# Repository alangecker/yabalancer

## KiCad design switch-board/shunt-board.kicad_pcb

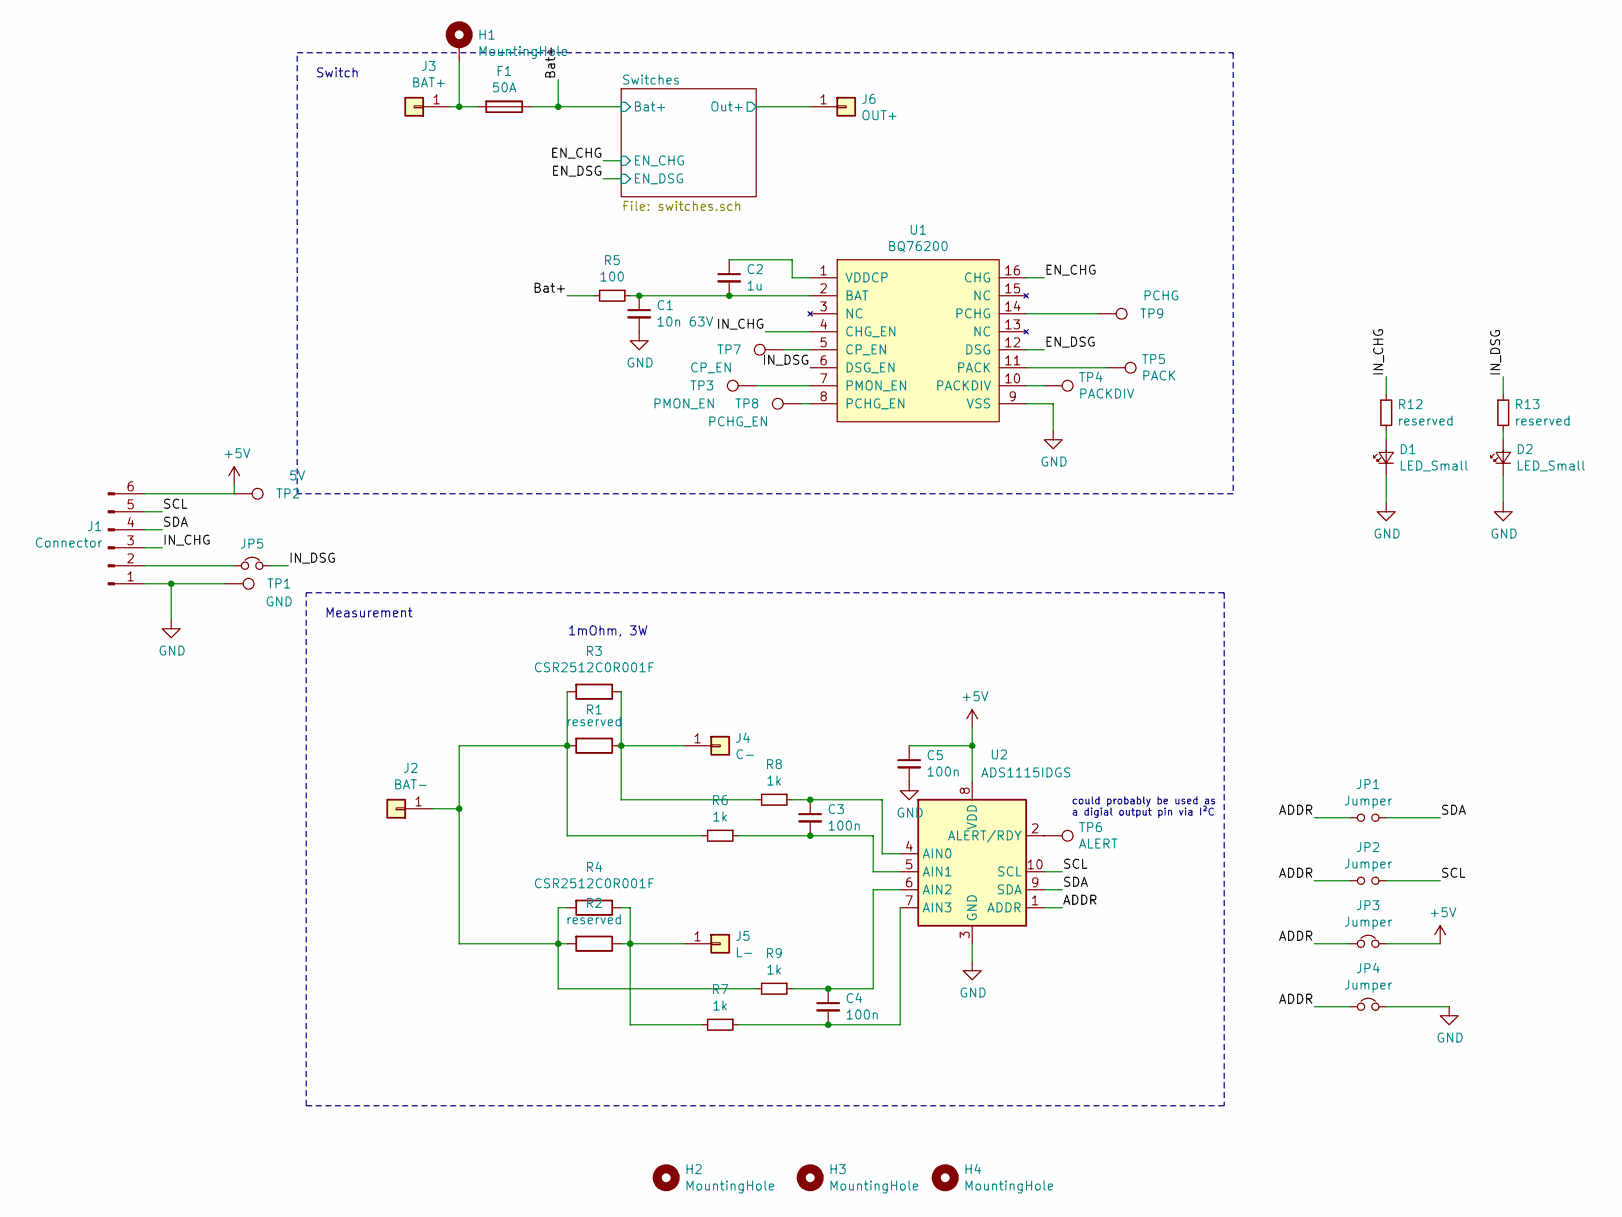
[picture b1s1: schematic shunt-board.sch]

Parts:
C1: 10n 63V; C_0805_2012Metric_Pad1.15x1.40mm_HandSolder
C2: 1u; C_0805_2012Metric_Pad1.15x1.40mm_HandSolder
C3, C4, C5: 100n; C_0805_2012Metric_Pad1.15x1.40mm_HandSolder
D1, D2: LED_Small; LED_1206_3216Metric_Pad1.42x1.75mm_HandSolder
F1: 50A; midiFuseHolder
H1, H2, H3, H4: MountingHole; MountingHole_4mm_Pad_Via
J1: Connector; JST_XH_B6B-XH-A_1x06_P2.50mm_Vertical
J2: BAT-; M5_screw_terminal
J3: BAT+; M5_screw_terminal
J4: C-; M5_screw_terminal
J5: L-; M5_screw_terminal
J6: OUT+; M5_screw_terminal
JP1, JP2: Jumper; SolderJumper-2_P1.3mm_Open_RoundedPad1.0x1.5mm
JP3, JP4: Jumper; SolderJumper-2_P1.3mm_Bridged_RoundedPad1.0x1.5mm
JP5: Jumper_NC_Small; SolderJumper-2_P1.3mm_Bridged2Bar_RoundedPad1.0x1.5mm
R1, R2: reserved; R_2512_6332Metric_Pad1.52x3.35mm_HandSolder
R3, R4: CSR2512C0R001F; R_2512_6332Metric_Pad1.52x3.35mm_HandSolder
R5: 100; R_0805_2012Metric
R6, R7, R8, R9: 1k; R_0805_2012Metric
R12, R13: reserved; R_0805_2012Metric_Pad1.15x1.40mm_HandSolder
TP1: GND; TestPoint_Pad_1.0x1.0mm
TP2: 5V; TestPoint_Pad_1.0x1.0mm
TP3: PMON_EN; TestPoint_Pad_1.0x1.0mm
TP4: PACKDIV; TestPoint_Pad_1.0x1.0mm
TP5: PACK; TestPoint_Pad_1.0x1.0mm
TP6: ALERT; TestPoint_Pad_1.0x1.0mm
TP7: CP_EN; TestPoint_Pad_1.0x1.0mm
TP8: PCHG_EN; TestPoint_Pad_1.0x1.0mm
TP9: PCHG; TestPoint_Pad_1.0x1.0mm
U1: BQ76200; TSSOP-16_4.4x5mm_P0.65mm
U2: ADS1115IDGS; TSSOP-10_3x3mm_P0.5mm

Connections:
+5V: C5.1, J1.6, JP3.2, TP2.1, U2.8 (VDD)
/ADDR: JP1.1, JP2.1, JP3.1, JP4.1, U2.1 (ADDR)
/Bat+: F1.1, R5.2; also elsewhere on the board
/EN_CHG: U1.16 (CHG); also elsewhere on the board
/EN_DSG: U1.12 (DSG); also elsewhere on the board
/IN_CHG: J1.3, R12.1, U1.4 (CHG_EN)
/IN_DSG: JP5.2, R13.1, U1.6 (DSG_EN)
/SCL: J1.5, JP2.2, U2.10 (SCL)
/SDA: J1.4, JP1.2, U2.9 (SDA)
/Switches/Out+: J6.1; also elsewhere on the board
GND: C1.2, C5.2, D1.1 (K), D2.1 (K), J1.1, JP4.2, TP1.1, U1.9 (VSS), U2.3 (GND)
unnamed: C1.1, C2.2, R5.1, U1.2 (BAT)
unnamed: C2.1, U1.1 (VDDCP)
unnamed: C3.1, R8.1, U2.4 (AIN0)
unnamed: C3.2, R6.1, U2.5 (AIN1)
unnamed: C4.1, R9.1, U2.6 (AIN2)
unnamed: C4.2, R7.1, U2.7 (AIN3)
unnamed: D1.2 (A), R12.2
unnamed: D2.2 (A), R13.2
unnamed: F1.2, H1.1, J3.1
unnamed: J1.2, JP5.1
unnamed: J2.1, R1.2, R2.2, R3.2, R4.2, R6.2, R9.2
unnamed: J4.1, R1.1, R3.1, R8.2
unnamed: J5.1, R2.1, R4.1, R7.2
unnamed: TP3.1, U1.7 (PMON_EN)
unnamed: TP4.1, U1.10 (PACKDIV)
unnamed: TP5.1, U1.11 (PACK)
unnamed: TP6.1, U2.2 (ALERT/RDY)
unnamed: TP7.1, U1.5 (CP_EN)
unnamed: TP8.1, U1.8 (PCHG_EN)
unnamed: TP9.1, U1.14 (PCHG)

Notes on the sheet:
Measurement
Switch
1mOhm, 3W
could probably be used as a digial output pin via I²C

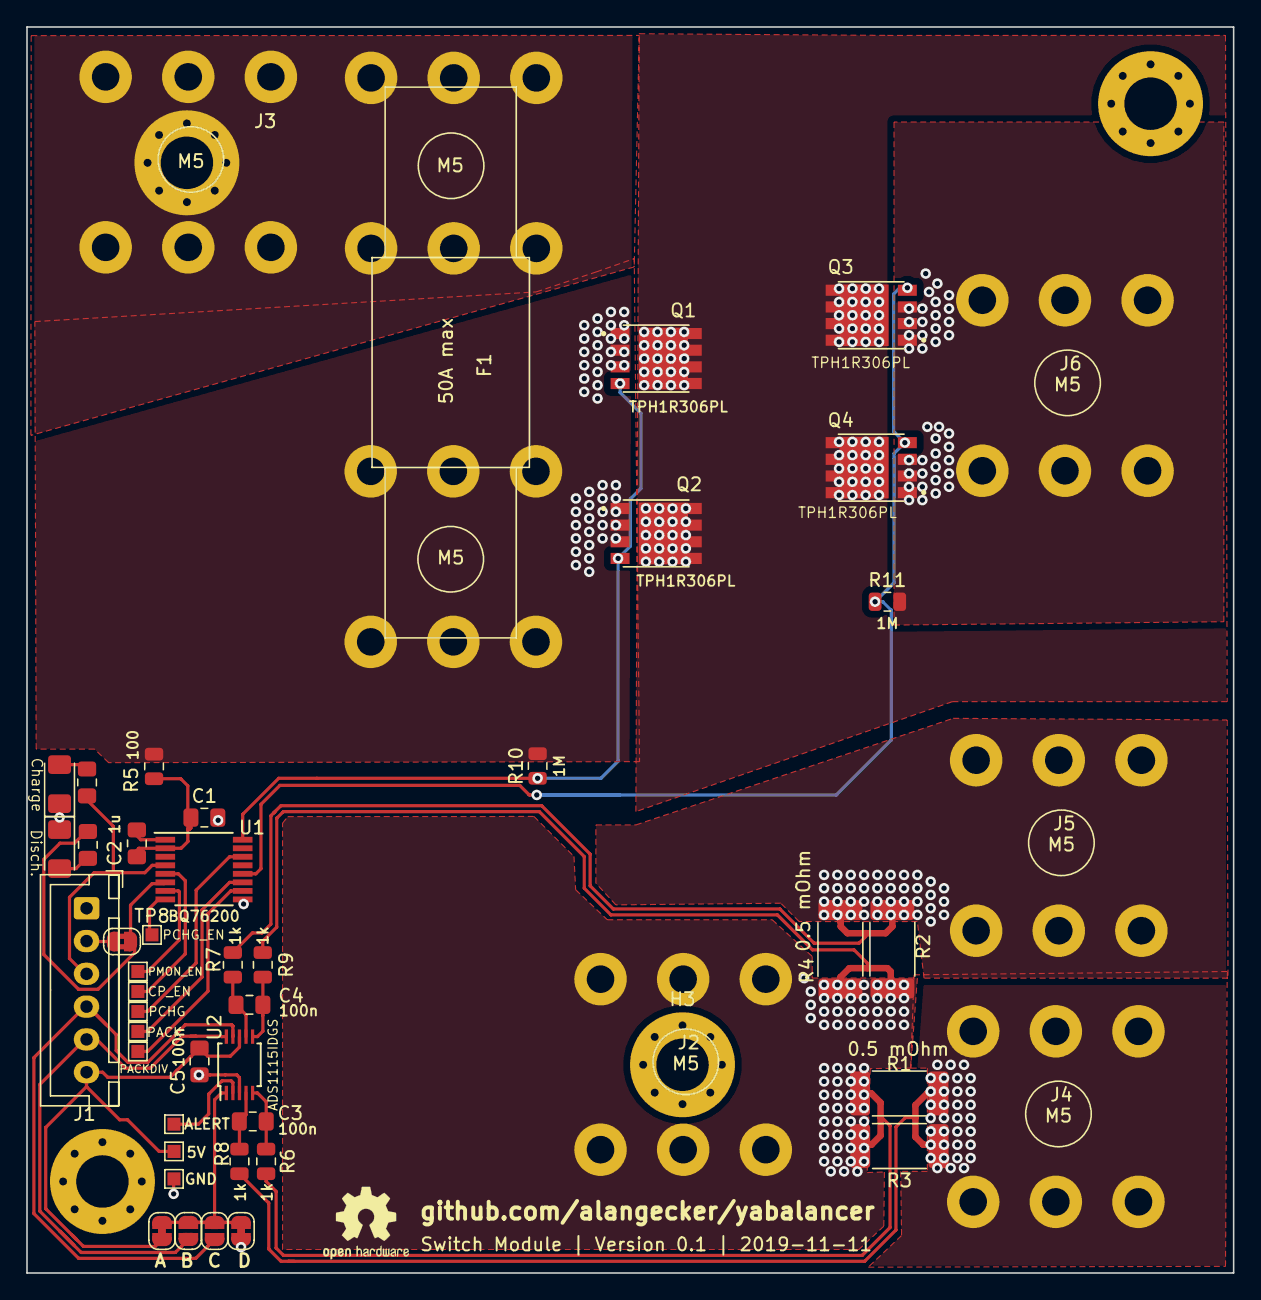
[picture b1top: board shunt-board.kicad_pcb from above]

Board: 2 copper layers, 92.0 x 95.0 mm, 51 parts (0 on the bottom side), 32 nets.

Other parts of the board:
Q1, Q2, Q3, Q4: TPH1R306PL; TRANS_TPHR8504PL,L1Q
R10, R11: 1M; R_0805_2012Metric

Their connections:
/Bat+: Q1.1, Q1.2, Q1.3, Q2.1, Q2.2, Q2.3, R10.2; also elsewhere on the board
/EN_CHG: Q1.4, Q2.4, R10.1; also elsewhere on the board
/EN_DSG: Q3.4, Q4.4, R11.1; also elsewhere on the board
/Switches/Out+: Q3.1, Q3.2, Q3.3, Q4.1, Q4.2, Q4.3, R11.2; also elsewhere on the board
unnamed: Q1.5, Q1.6, Q1.7, Q1.8, Q1.9, Q2.5, Q2.6, Q2.7, Q2.8, Q2.9, Q3.5, Q3.6, Q3.7, Q3.8, Q3.9, Q4.5, Q4.6, Q4.7, Q4.8, Q4.9

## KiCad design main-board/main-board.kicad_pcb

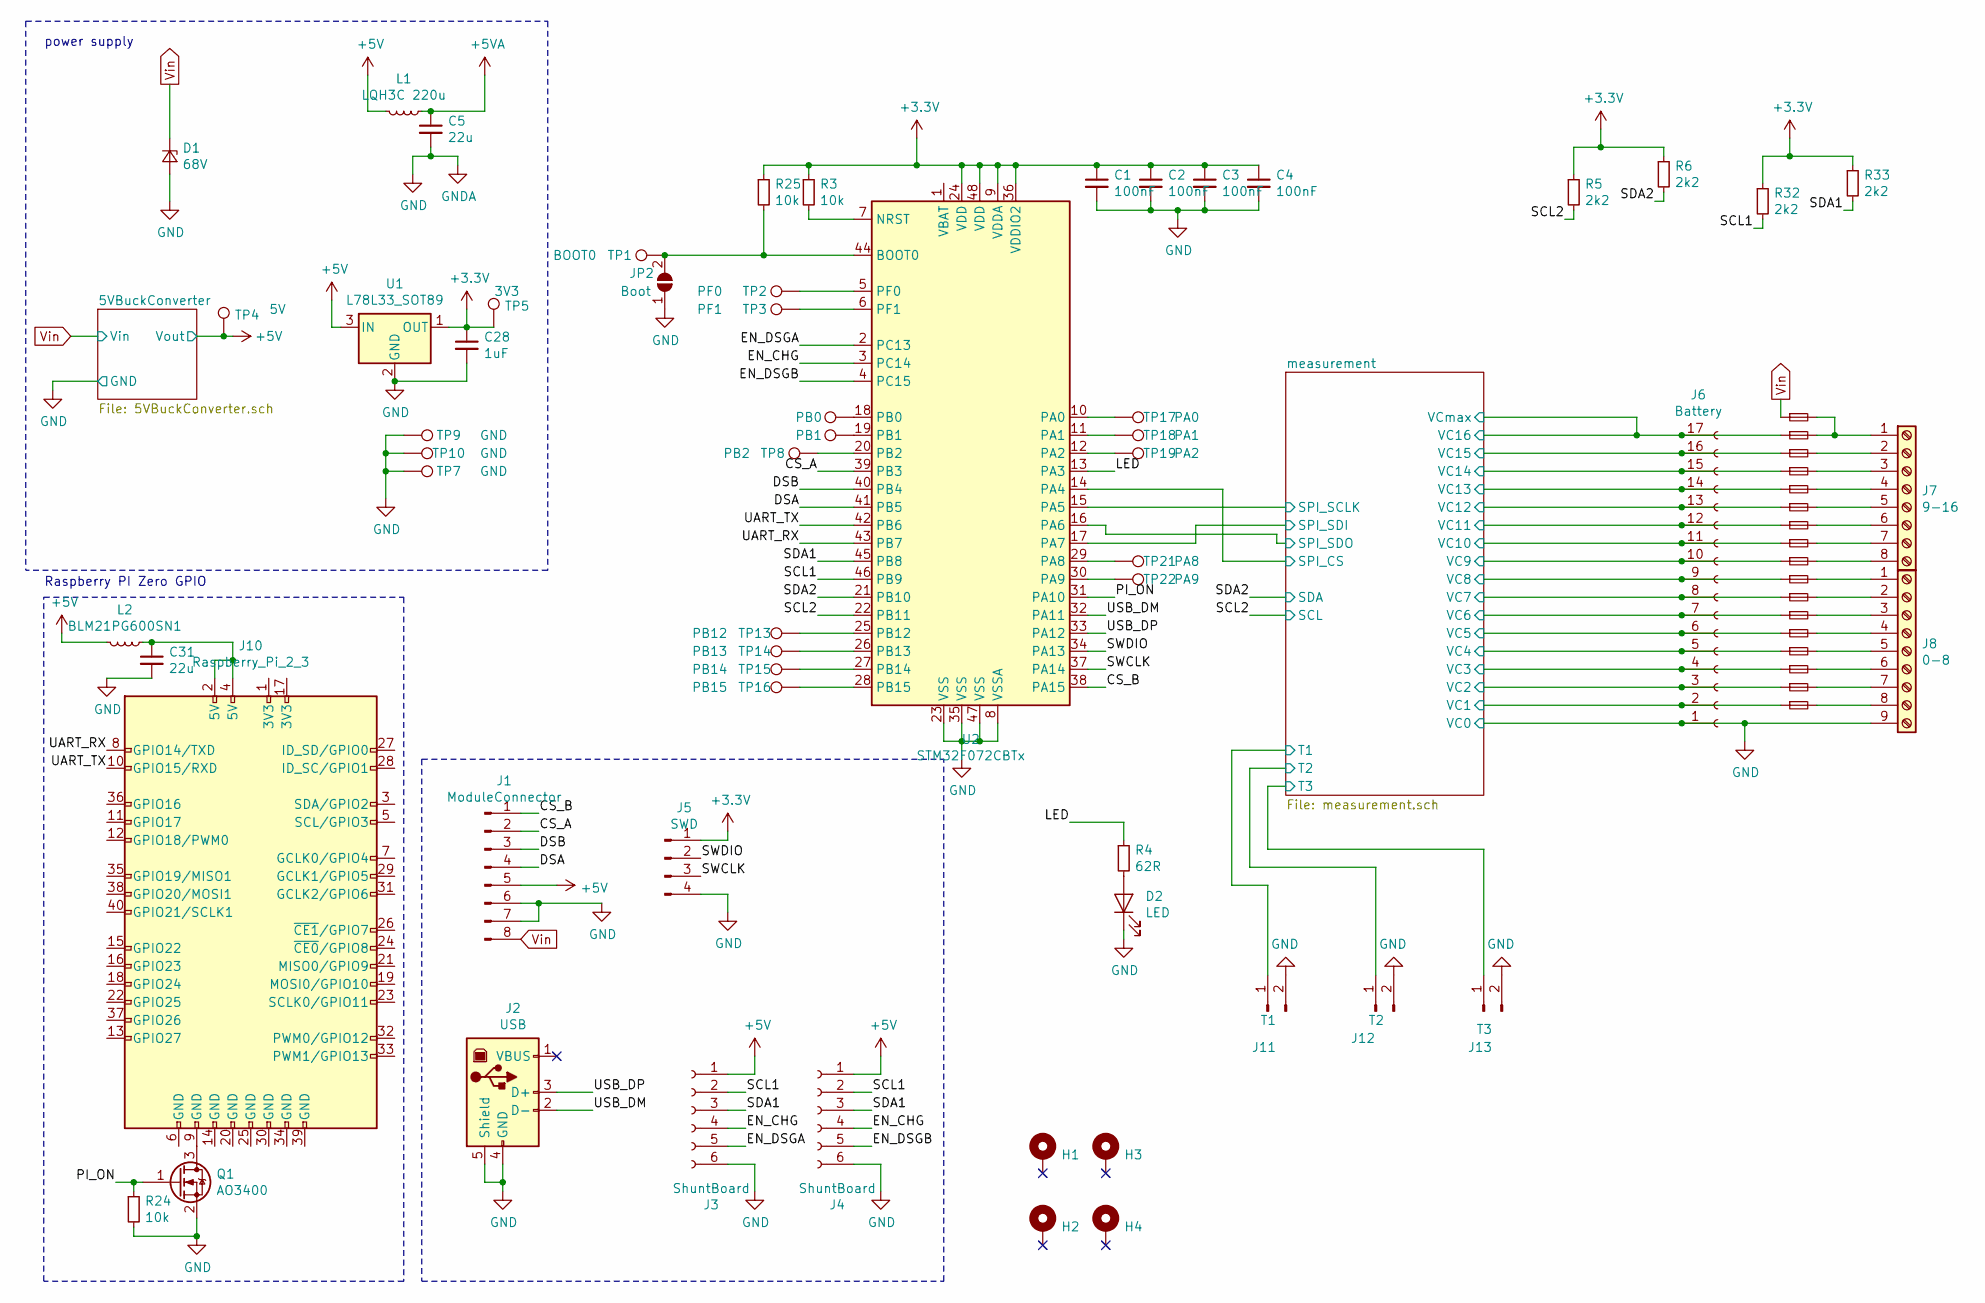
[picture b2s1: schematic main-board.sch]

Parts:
C1, C2, C3, C4: 100nF; C_0805_2012Metric
C5, C31: 22u; C_1206_3216Metric
C28: 1uF; C_0805_2012Metric
D1: 68V; D_SMB-SMC_Universal_Handsoldering
D2: LED; LED_D5.0mm
F1, F2, F3, F4, F5, F6, F7, F8, F9, F10, F11, F12, F13, F14, F15, F16: 2A; R_1812_4532Metric_Pad1.30x3.40mm_HandSolder
F17: 1A; R_1812_4532Metric_Pad1.30x3.40mm_HandSolder
H1, H2, H3, H4: MountingHole; MountingHole_3.2mm_M3_DIN965_Pad
J1: ModuleConnector; PinHeader_1x08_P2.54mm_Vertical
J2: USB; USB_B_OST_USB-B1HSxx_Horizontal
J3, J4: ShuntBoard; JST_XH_S6B-XH-A_1x06_P2.50mm_Horizontal
J5: SWD; PinHeader_1x04_P2.54mm_Vertical
J6: Battery; PinHeader_1x17_P2.54mm_Vertical
J7: 9-16; TerminalBlock_RND_205-00238_1x08_P5.08mm_Horizontal
J8: 0-8; TerminalBlock_RND_205-00239_1x09_P5.08mm_Horizontal
J10: Raspberry_Pi_2_3; Raspberry_Pi_Zero_Socketed_THT_FaceDown_MountingHoles
J11: T1; JST_XH_S2B-XH-A_1x02_P2.50mm_Horizontal
J12: T2; JST_XH_S2B-XH-A_1x02_P2.50mm_Horizontal
J13: T3; JST_XH_S2B-XH-A_1x02_P2.50mm_Horizontal
JP2: Boot; SolderJumper-2_P1.3mm_Open_RoundedPad1.0x1.5mm
L1: LQH3C 220u; L_1210_3225Metric_Pad1.42x2.65mm_HandSolder
L2: BLM21PG600SN1; L_0805_2012Metric_Pad1.15x1.40mm_HandSolder
PB0: PB8; TestPoint_THTPad_2.0x2.0mm_Drill1.0mm
PB1: PB9; TestPoint_THTPad_2.0x2.0mm_Drill1.0mm
Q1: AO3400; SOT-23
R3, R24, R25: 10k; R_0805_2012Metric
R4: 62R; R_0805_2012Metric
R5, R6, R32, R33: 2k2; R_0805_2012Metric
TP1: BOOT0; TestPoint_THTPad_2.5x2.5mm_Drill1.2mm
TP2: PF0; TestPoint_THTPad_2.0x2.0mm_Drill1.0mm
TP3: PF1; TestPoint_THTPad_2.0x2.0mm_Drill1.0mm
TP4: 5V; TestPoint_THTPad_2.0x2.0mm_Drill1.0mm
TP5: 3V3; TestPoint_THTPad_2.0x2.0mm_Drill1.0mm
TP7, TP9, TP10: GND; TestPoint_THTPad_2.0x2.0mm_Drill1.0mm
TP8: PB2; TestPoint_THTPad_2.0x2.0mm_Drill1.0mm
TP13: PB12; TestPoint_THTPad_2.0x2.0mm_Drill1.0mm
TP14: PB13; TestPoint_THTPad_2.0x2.0mm_Drill1.0mm
TP15: PB14; TestPoint_THTPad_2.0x2.0mm_Drill1.0mm
TP16: PB15; TestPoint_THTPad_2.0x2.0mm_Drill1.0mm
TP17: PA0; TestPoint_THTPad_2.0x2.0mm_Drill1.0mm
TP18: PA1; TestPoint_THTPad_2.0x2.0mm_Drill1.0mm
TP19: PA2; TestPoint_THTPad_2.0x2.0mm_Drill1.0mm
TP21: PA8; TestPoint_THTPad_2.0x2.0mm_Drill1.0mm
TP22: PA9; TestPoint_THTPad_2.0x2.0mm_Drill1.0mm
U1: L78L33_SOT89; SOT-89-3
U2: STM32F072CBTx; LQFP-48_7x7mm_P0.5mm

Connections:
+3V3: C1.1, C2.1, C3.1, C4.1, C28.1, J5.1, R3.1, R5.1, R6.1, R25.1, R32.1, R33.1, TP5.1, U1.1 (OUT), U2.9 (VDDA), U2.24 (VDD), U2.36 (VDDIO2), U2.48 (VDD); also elsewhere on the board
+5V: J1.5, J3.1, J4.1, L1.2, L2.2, TP4.1, U1.3 (IN); also elsewhere on the board
+5VA: C5.1, L1.1; also elsewhere on the board
/CS_A: J1.2, U2.39 (PB3)
/CS_B: J1.1, U2.38 (PA15)
/DSA: J1.4, U2.41 (PB5)
/DSB: J1.3, U2.40 (PB4)
/EN_CHG: J3.4, J4.4, U2.3 (PC14)
/EN_DSGA: J3.5, U2.2 (PC13)
/EN_DSGB: J4.5, U2.4 (PC15)
/LED: R4.1, U2.13 (PA3)
/PI_ON: Q1.1 (G), R24.1, U2.31 (PA10)
/SCL1: J3.2, J4.2, R32.2, U2.46 (PB9)
/SCL2: R5.2, U2.22 (PB11); also elsewhere on the board
/SDA1: J3.3, J4.3, R33.2, U2.45 (PB8)
/SDA2: R6.2, U2.21 (PB10); also elsewhere on the board
/SWCLK: J5.3, U2.37 (PA14)
/SWDIO: J5.2, U2.34 (PA13)
/UART_RX: J10.8 (GPIO14/TXD), U2.43 (PB7)
/UART_TX: J10.10 (GPIO15/RXD), U2.42 (PB6)
/USB_DM: J2.2 (D-), U2.32 (PA11)
/USB_DP: J2.3 (D+), U2.33 (PA12)
/measurement/SPI_CS: U2.14 (PA4); also elsewhere on the board
/measurement/SPI_SCLK: U2.15 (PA5); also elsewhere on the board
/measurement/SPI_SDI: U2.17 (PA7); also elsewhere on the board
/measurement/SPI_SDO: U2.16 (PA6); also elsewhere on the board
/measurement/T1: J11.1; also elsewhere on the board
/measurement/T2: J12.1; also elsewhere on the board
/measurement/T3: J13.1; also elsewhere on the board
/measurement/VC1: F16.1, J6.2; also elsewhere on the board
/measurement/VC2: F15.1, J6.3; also elsewhere on the board
/measurement/VC3: F14.1, J6.4; also elsewhere on the board
/measurement/VC4: F13.1, J6.5; also elsewhere on the board
/measurement/VC5: F12.1, J6.6; also elsewhere on the board
/measurement/VC6: F11.1, J6.7; also elsewhere on the board
/measurement/VC7: F10.1, J6.8; also elsewhere on the board
/measurement/VC8: F9.1, J6.9; also elsewhere on the board
/measurement/VC9: F8.1, J6.10; also elsewhere on the board
/measurement/VC10: F7.1, J6.11; also elsewhere on the board
/measurement/VC11: F6.1, J6.12; also elsewhere on the board
/measurement/VC12: F5.1, J6.13; also elsewhere on the board
/measurement/VC13: F4.1, J6.14; also elsewhere on the board
/measurement/VC14: F3.1, J6.15; also elsewhere on the board
/measurement/VC15: F2.1, J6.16; also elsewhere on the board
/measurement/VC16: F1.1, J6.17; also elsewhere on the board
GND: C1.2, C2.2, C3.2, C4.2, C5.2, C28.2, C31.2, D1.2 (A), D2.1 (K), J1.6, J1.7, J2.4 (GND), J2.5 (Shield), J3.6, J4.6, J5.4, J6.1, J8.9, J11.2, J12.2, J13.2, JP2.1 (A), Q1.2 (S), R24.2, TP7.1, TP9.1, TP10.1, U1.2 (GND), U2.8 (VSSA), U2.23 (VSS), U2.35 (VSS), U2.47 (VSS); also elsewhere on the board
unnamed: C31.1, J10.2 (5V), J10.4 (5V), L2.1
unnamed: D2.2 (A), R4.2
unnamed: F1.2, F17.2, J7.1
unnamed: F2.2, J7.2
unnamed: F3.2, J7.3
unnamed: F4.2, J7.4
unnamed: F5.2, J7.5
unnamed: F6.2, J7.6
unnamed: F7.2, J7.7
unnamed: F8.2, J7.8
unnamed: F9.2, J8.1
unnamed: F10.2, J8.2
unnamed: F11.2, J8.3
unnamed: F12.2, J8.4
unnamed: F13.2, J8.5
unnamed: F14.2, J8.6
unnamed: F15.2, J8.7
unnamed: F16.2, J8.8
unnamed: J10.9 (GND), Q1.3 (D)
unnamed: JP2.2 (B), R25.2, TP1.1, U2.44 (BOOT0)
unnamed: PB0.1, U2.18 (PB0)
unnamed: PB1.1, U2.19 (PB1)
unnamed: R3.2, U2.7 (NRST)
unnamed: TP2.1, U2.5 (PF0)
unnamed: TP3.1, U2.6 (PF1)
unnamed: TP8.1, U2.20 (PB2)
unnamed: TP13.1, U2.25 (PB12)
unnamed: TP14.1, U2.26 (PB13)
unnamed: TP15.1, U2.27 (PB14)
unnamed: TP16.1, U2.28 (PB15)
unnamed: TP17.1, U2.10 (PA0)
unnamed: TP18.1, U2.11 (PA1)
unnamed: TP19.1, U2.12 (PA2)
unnamed: TP21.1, U2.29 (PA8)
unnamed: TP22.1, U2.30 (PA9)
Vin: D1.1 (K), F17.1, J1.8; also elsewhere on the board

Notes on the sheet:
power supply
Raspberry PI Zero GPIO

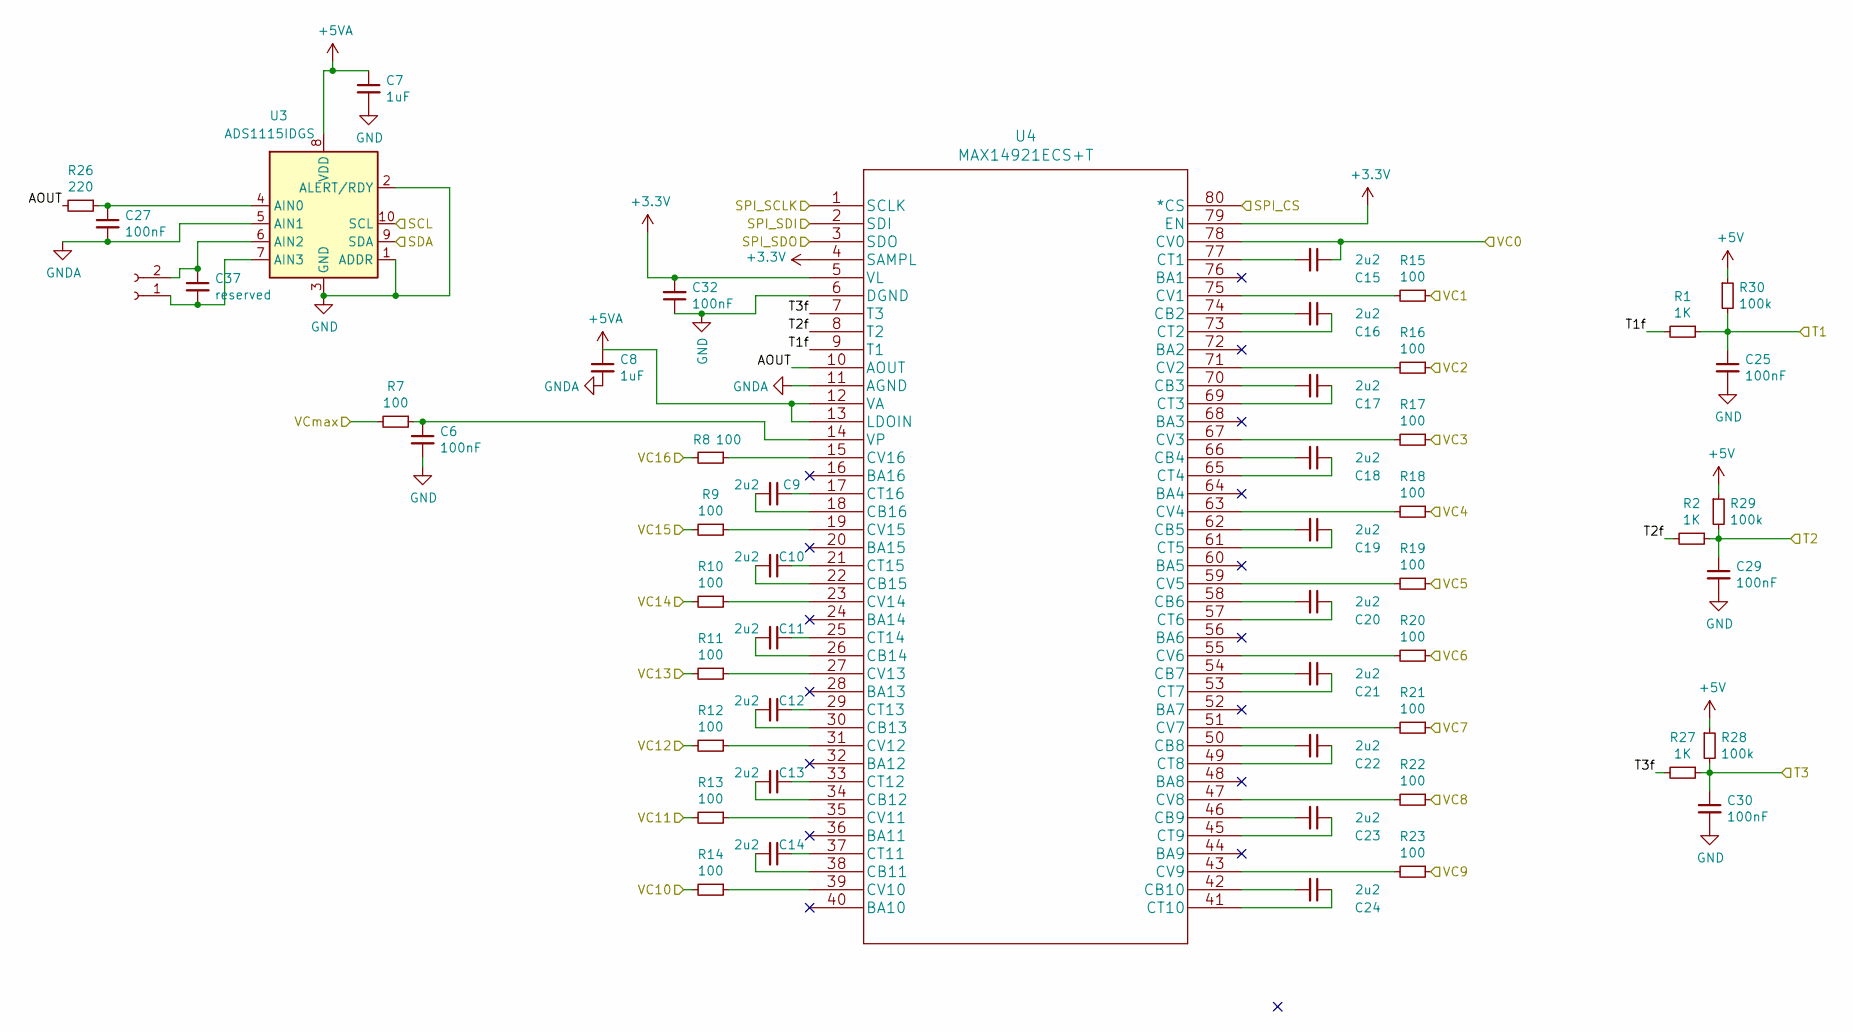
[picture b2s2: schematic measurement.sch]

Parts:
C6, C25, C27, C29, C30, C32: 100nF; C_0805_2012Metric
C7, C8: 1uF; C_0805_2012Metric
C9, C10, C11, C12, C13, C14, C15, C16, C17, C18, C19, C20, C21, C22, C23, C24: 2u2; C_0805_2012Metric
C37: reserved; C_0805_2012Metric
J9: Conn_01x02_Female; PinHeader_1x02_P2.54mm_Vertical
R1, R2, R27: 1K; C_0805_2012Metric
R7, R8, R9, R10, R11, R12, R13, R14, R15, R16, R17, R18, R19, R20, R21, R22, R23: 100; R_0805_2012Metric
R26: 220; R_0805_2012Metric
R28, R29, R30: 100k; C_0805_2012Metric
U3: ADS1115IDGS; MSOP-10_3x3mm_P0.5mm
U4: MAX14921ECS+T; TQFP-80_12x12mm_P0.5mm

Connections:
+3V3: C32.2, U4.4 (SAMPL), U4.5 (VL), U4.79 (EN); also elsewhere on the board
+5V: R28.1, R29.1, R30.1; also elsewhere on the board
+5VA: C7.1, C8.1, U3.8 (VDD), U4.12 (VA), U4.13 (LDOIN); also elsewhere on the board
/SCL2: U3.10 (SCL); also elsewhere on the board
/SDA2: U3.9 (SDA); also elsewhere on the board
/measurement/AOUT: R26.2, U4.10 (AOUT)
/measurement/SPI_CS: U4.80 (*CS); also elsewhere on the board
/measurement/SPI_SCLK: U4.1 (SCLK); also elsewhere on the board
/measurement/SPI_SDI: U4.2 (SDI); also elsewhere on the board
/measurement/SPI_SDO: U4.3 (SDO); also elsewhere on the board
/measurement/T1: C25.1, R1.1, R30.2; also elsewhere on the board
/measurement/T1f: R1.2, U4.9 (T1)
/measurement/T2: C29.1, R2.1, R29.2; also elsewhere on the board
/measurement/T2f: R2.2, U4.8 (T2)
/measurement/T3: C30.1, R27.1, R28.2; also elsewhere on the board
/measurement/T3f: R27.2, U4.7 (T3)
/measurement/VC1: R15.1; also elsewhere on the board
/measurement/VC2: R16.1; also elsewhere on the board
/measurement/VC3: R17.1; also elsewhere on the board
/measurement/VC4: R18.1; also elsewhere on the board
/measurement/VC5: R19.1; also elsewhere on the board
/measurement/VC6: R20.1; also elsewhere on the board
/measurement/VC7: R21.1; also elsewhere on the board
/measurement/VC8: R22.1; also elsewhere on the board
/measurement/VC9: R23.1; also elsewhere on the board
/measurement/VC10: R14.2; also elsewhere on the board
/measurement/VC11: R13.2; also elsewhere on the board
/measurement/VC12: R12.2; also elsewhere on the board
/measurement/VC13: R11.2; also elsewhere on the board
/measurement/VC14: R10.2; also elsewhere on the board
/measurement/VC15: R9.2; also elsewhere on the board
/measurement/VC16: R7.2, R8.2; also elsewhere on the board
GND: C6.2, C7.2, C8.2, C15.1, C25.2, C27.2, C29.2, C30.2, C32.1, U3.1 (ADDR), U3.2 (ALERT/RDY), U3.3 (GND), U3.5 (AIN1), U4.6 (DGND), U4.11 (AGND), U4.78 (CV0); also elsewhere on the board
unnamed: C6.1, R7.1, U4.14 (VP)
unnamed: C9.1, U4.17 (CT16)
unnamed: C9.2, U4.18 (CB16)
unnamed: C10.1, U4.21 (CT15)
unnamed: C10.2, U4.22 (CB15)
unnamed: C11.1, U4.25 (CT14)
unnamed: C11.2, U4.26 (CB14)
unnamed: C12.1, U4.29 (CT13)
unnamed: C12.2, U4.30 (CB13)
unnamed: C13.1, U4.33 (CT12)
unnamed: C13.2, U4.34 (CB12)
unnamed: C14.1, U4.37 (CT11)
unnamed: C14.2, U4.38 (CB11)
unnamed: C15.2, U4.77 (CT1)
unnamed: C16.1, U4.73 (CT2)
unnamed: C16.2, U4.74 (CB2)
unnamed: C17.1, U4.69 (CT3)
unnamed: C17.2, U4.70 (CB3)
unnamed: C18.1, U4.65 (CT4)
unnamed: C18.2, U4.66 (CB4)
unnamed: C19.1, U4.61 (CT5)
unnamed: C19.2, U4.62 (CB5)
unnamed: C20.1, U4.57 (CT6)
unnamed: C20.2, U4.58 (CB6)
unnamed: C21.1, U4.53 (CT7)
unnamed: C21.2, U4.54 (CB7)
unnamed: C22.1, U4.49 (CT8)
unnamed: C22.2, U4.50 (CB8)
unnamed: C23.1, U4.45 (CT9)
unnamed: C23.2, U4.46 (CB9)
unnamed: C24.1, U4.41 (CT10)
unnamed: C24.2, U4.42 (CB10)
unnamed: C27.1, R26.1, U3.4 (AIN0)
unnamed: C37.1, J9.2, U3.6 (AIN2)
unnamed: C37.2, J9.1, U3.7 (AIN3)
unnamed: R8.1, U4.15 (CV16)
unnamed: R9.1, U4.19 (CV15)
unnamed: R10.1, U4.23 (CV14)
unnamed: R11.1, U4.27 (CV13)
unnamed: R12.1, U4.31 (CV12)
unnamed: R13.1, U4.35 (CV11)
unnamed: R14.1, U4.39 (CV10)
unnamed: R15.2, U4.75 (CV1)
unnamed: R16.2, U4.71 (CV2)
unnamed: R17.2, U4.67 (CV3)
unnamed: R18.2, U4.63 (CV4)
unnamed: R19.2, U4.59 (CV5)
unnamed: R20.2, U4.55 (CV6)
unnamed: R21.2, U4.51 (CV7)
unnamed: R22.2, U4.47 (CV8)
unnamed: R23.2, U4.43 (CV9)

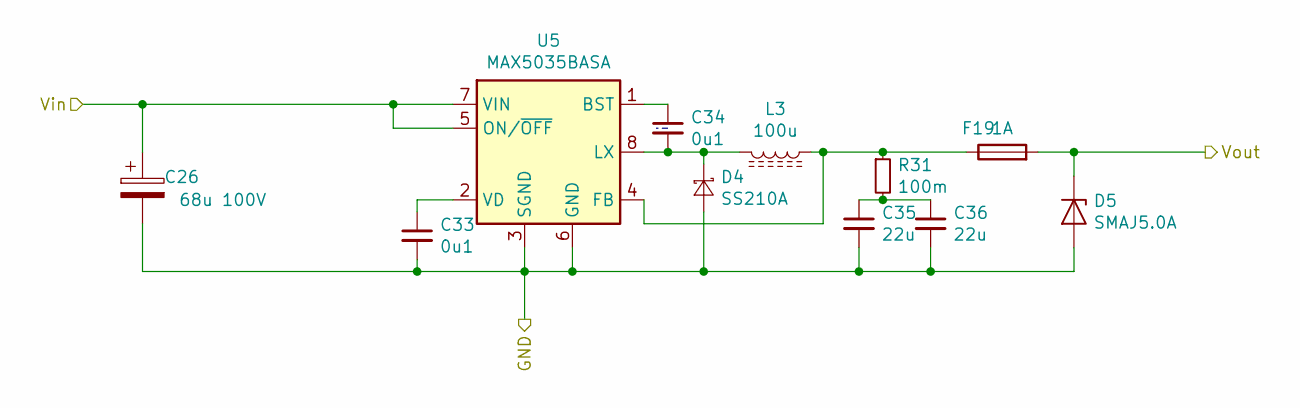
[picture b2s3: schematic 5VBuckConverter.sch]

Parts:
C26: 68u 100V; CP_Radial_D12.5mm_P5.00mm
C33, C34: 0u1; C_0805_2012Metric_Pad1.15x1.40mm_HandSolder
C35, C36: 22u; C_1206_3216Metric
D4: SS210A; D_SMA_Handsoldering
D5: SMAJ5.0A; D_SMA_Handsoldering
F19: 1A; R_2512_6332Metric
L3: 100u; L_Fastron_PISR_Handsoldering
R31: 100m; R_0805_2012Metric
U5: MAX5035BASA; SOIC-8_3.9x4.9mm_P1.27mm

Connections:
+5V: D5.1 (K), F19.2; also elsewhere on the board
GND: C26.2, C33.2, C35.2, C36.2, D4.2 (A), D5.2 (A), U5.3 (SGND), U5.6 (GND); also elsewhere on the board
unnamed: C33.1, U5.2 (VD)
unnamed: C34.1, U5.1 (BST)
unnamed: C34.2, D4.1 (K), L3.2, U5.8 (LX)
unnamed: C35.1, C36.1, R31.2
unnamed: F19.1, L3.1, R31.1, U5.4 (FB)
Vin: C26.1, U5.5 (ON/~OFF~), U5.7 (VIN); also elsewhere on the board

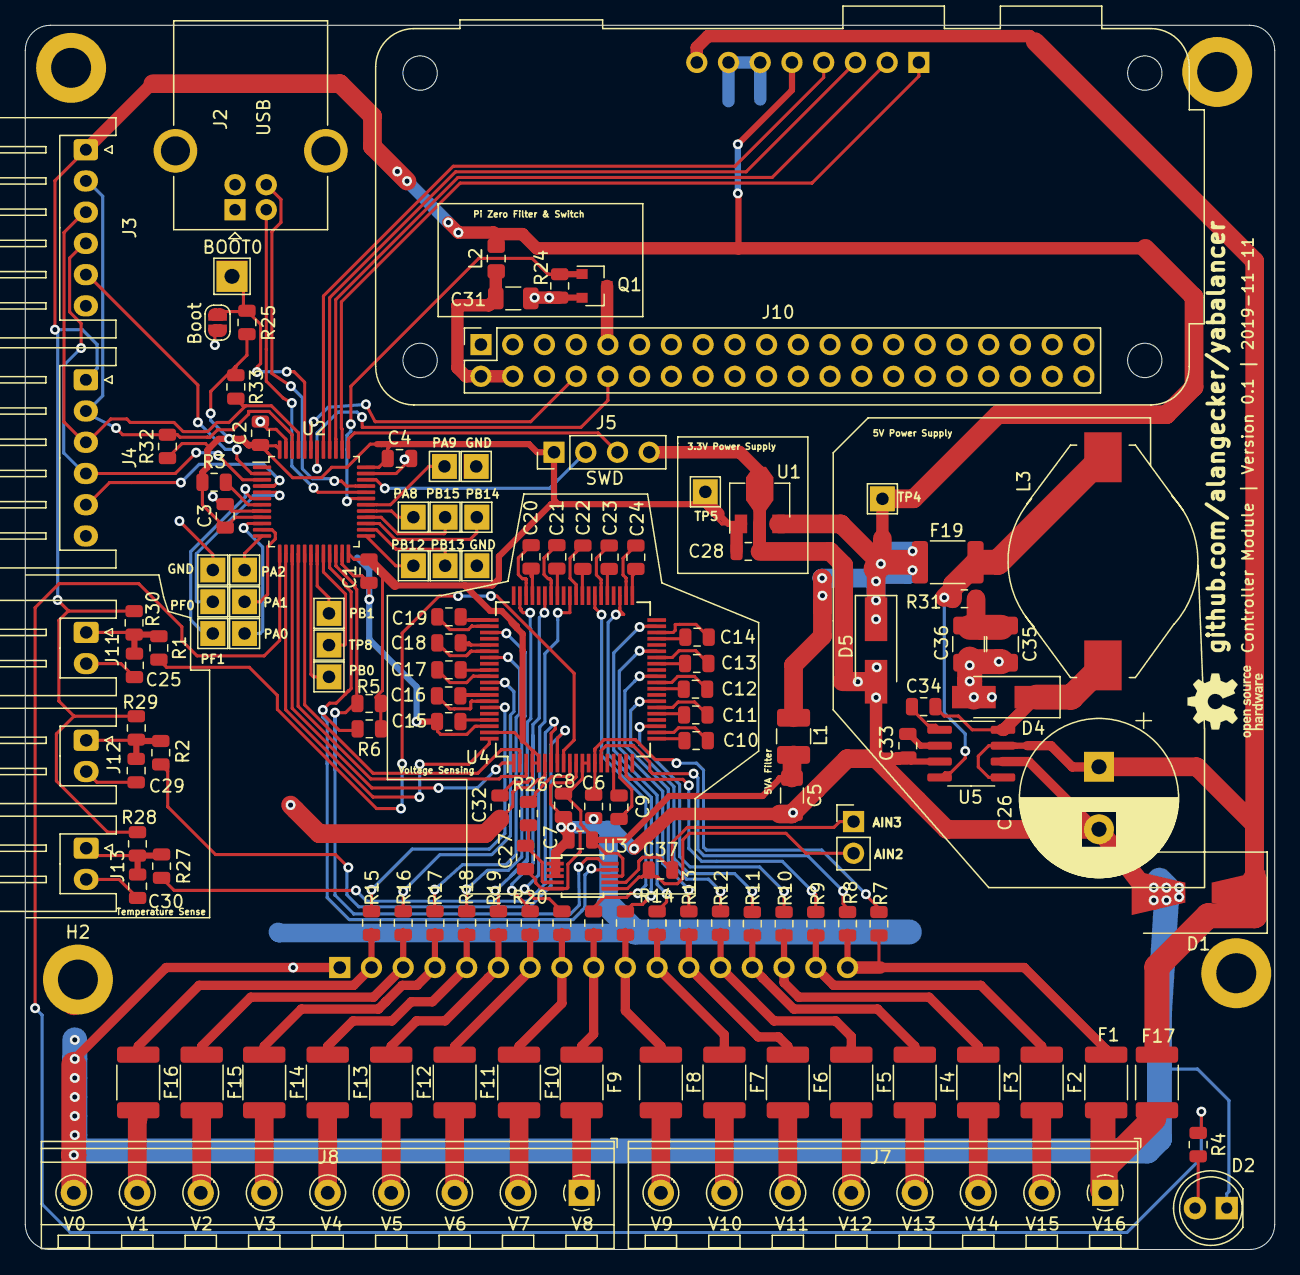
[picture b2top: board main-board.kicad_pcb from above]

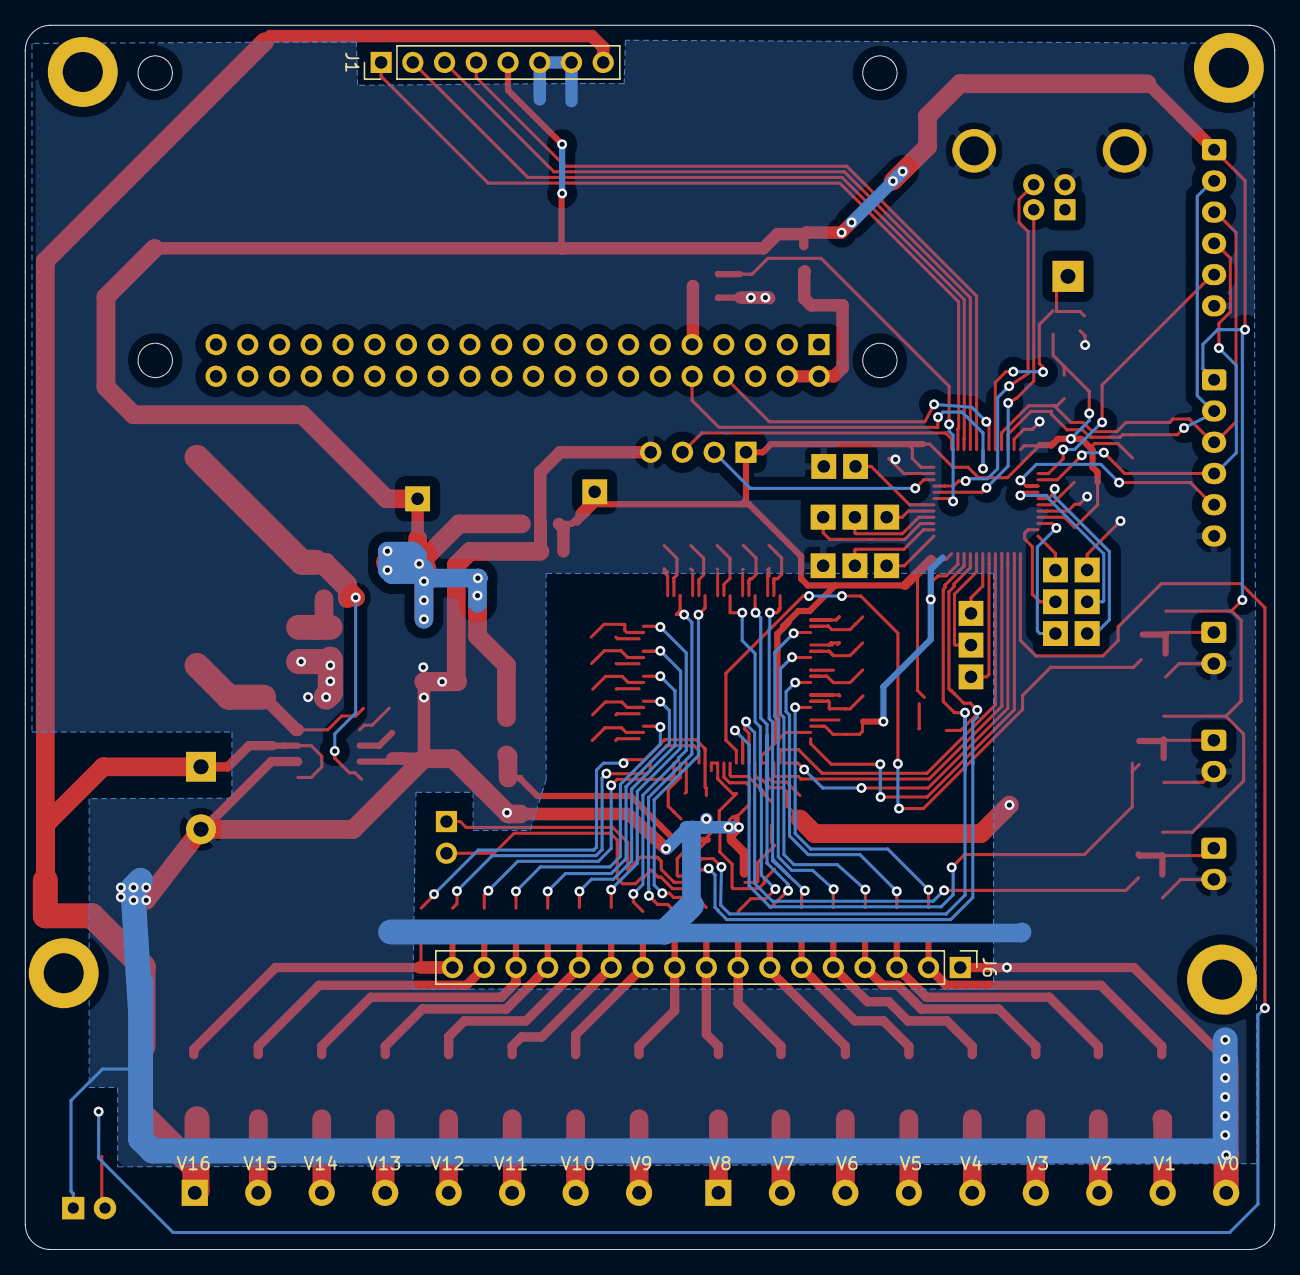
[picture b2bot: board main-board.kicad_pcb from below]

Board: 2 copper layers, 100.0 x 98.0 mm, 139 parts (2 on the bottom side), 142 nets.
